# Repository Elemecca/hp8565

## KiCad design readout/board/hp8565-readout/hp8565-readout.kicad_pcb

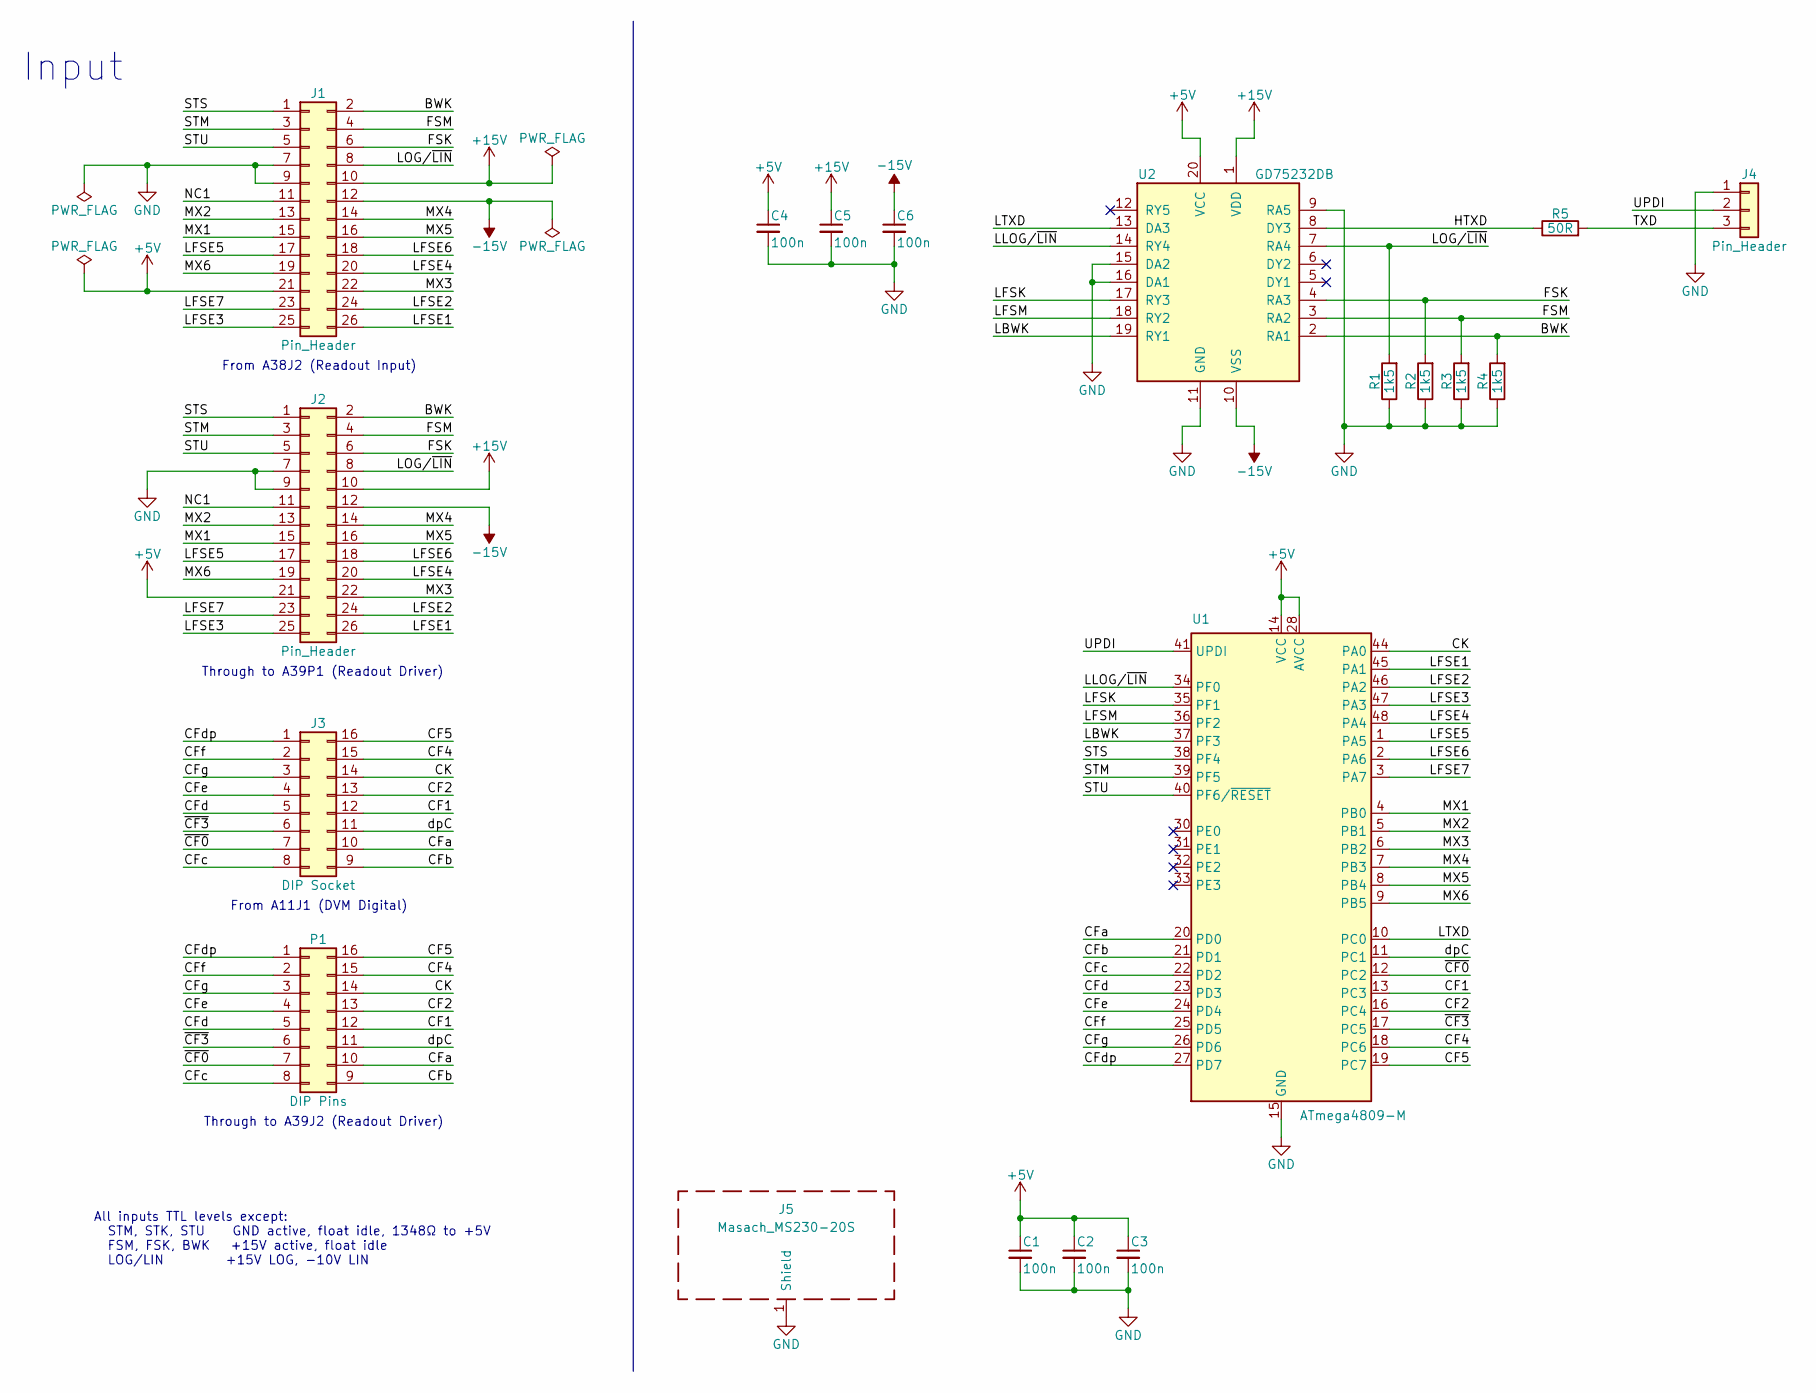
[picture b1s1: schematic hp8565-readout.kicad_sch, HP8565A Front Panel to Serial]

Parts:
C1, C2, C3, C4, C5, C6: 100n; C_0402_1005Metric
J1, J2: Pin_Header; PinHeader_2x13_P2.54mm_Vertical
J3: DIP Socket; DIP-16_W7.62mm_Socket
J4: Pin_Header; PinHeader_1x03_P2.54mm_Horizontal
J5: Masach_MS230-20S; Masach_MS230-20
P1: DIP Pins; DIP-16_W7.62mm
R1, R2, R3, R4: 1k5; R_0402_1005Metric
R5: 50R; R_0402_1005Metric
U1: ATmega4809-M; UQFN-48-1EP_6x6mm_P0.4mm_EP4.62x4.62mm
U2: GD75232DB; SSOP-20_4.4x6.5mm_P0.65mm

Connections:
+5V: C1.1, C2.1, C3.1, C4.1, J1.21, J2.21, U1.14 (VCC), U1.28 (AVCC), U1.42 (VCC), U2.20 (VCC)
+15V: C5.1, J1.10, J2.10, U2.1 (VDD)
-15V: C6.1, J1.12, J2.12, U2.10 (VSS)
/BWK: J1.2, J2.2, R4.2, U2.2 (RA1)
/CF1: J3.12, P1.12, U1.13 (PC3)
/CF2: J3.13, P1.13, U1.16 (PC4)
/CF4: J3.15, P1.15, U1.18 (PC6)
/CF5: J3.16, P1.16, U1.19 (PC7)
/CFa: J3.10, P1.10, U1.20 (PD0)
/CFb: J3.9, P1.9, U1.21 (PD1)
/CFc: J3.8, P1.8, U1.22 (PD2)
/CFd: J3.5, P1.5, U1.23 (PD3)
/CFdp: J3.1, P1.1, U1.27 (PD7)
/CFe: J3.4, P1.4, U1.24 (PD4)
/CFf: J3.2, P1.2, U1.25 (PD5)
/CFg: J3.3, P1.3, U1.26 (PD6)
/CK: J3.14, P1.14, U1.44 (PA0)
/FSK: J1.6, J2.6, R2.2, U2.4 (RA3)
/FSM: J1.4, J2.4, R3.2, U2.3 (RA2)
/HTXD: R5.1, U2.8 (DY3)
/LBWK: U1.37 (PF3), U2.19 (RY1)
/LFSE1: J1.26, J2.26, U1.45 (PA1)
/LFSE2: J1.24, J2.24, U1.46 (PA2)
/LFSE3: J1.25, J2.25, U1.47 (PA3)
/LFSE4: J1.20, J2.20, U1.48 (PA4)
/LFSE5: J1.17, J2.17, U1.1 (PA5)
/LFSE6: J1.18, J2.18, U1.2 (PA6)
/LFSE7: J1.23, J2.23, U1.3 (PA7)
/LFSK: U1.35 (PF1), U2.17 (RY3)
/LFSM: U1.36 (PF2), U2.18 (RY2)
/LLOG/~LIN: U1.34 (PF0), U2.14 (RY4)
/LOG/~LIN: J1.8, J2.8, R1.2, U2.7 (RA4)
/LTXD: U1.10 (PC0), U2.13 (DA3)
/MX1: J1.15, J2.15, U1.4 (PB0)
/MX2: J1.13, J2.13, U1.5 (PB1)
/MX3: J1.22, J2.22, U1.6 (PB2)
/MX4: J1.14, J2.14, U1.7 (PB3)
/MX5: J1.16, J2.16, U1.8 (PB4)
/MX6: J1.19, J2.19, U1.9 (PB5)
/NC1: J1.11, J2.11
/STM: J1.3, J2.3, U1.39 (PF5)
/STS: J1.1, J2.1, U1.38 (PF4)
/STU: J1.5, J2.5, U1.40 (PF6/~RESET)
/TXD: J4.3, R5.2
/UPDI: J4.2, U1.41 (UPDI)
/dpC: J3.11, P1.11, U1.11 (PC1)
/~CF0: J3.7, P1.7, U1.12 (PC2)
/~CF3: J3.6, P1.6, U1.17 (PC5)
GND: C1.2, C2.2, C3.2, C4.2, C5.2, C6.2, J1.7, J1.9, J2.7, J2.9, J4.1, J5.1 (Shield), R1.1, R2.1, R3.1, R4.1, U1.15 (GND), U1.29 (GND), U1.43 (GND), U1.49 (GND), U2.9 (RA5), U2.11 (GND), U2.15 (DA2), U2.16 (DA1)

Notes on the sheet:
From A38J2 (Readout Input)
From A11J1 (DVM Digital)
Through to A39J2 (Readout Driver)
Input
Through to A39P1 (Readout Driver)
All inputs TTL levels except: STM, STK, STU GND active, float idle, 1348Ω to +5V FSM, FSK, BWK +15V active, float idle LOG/LIN +15V LOG, -10V LIN

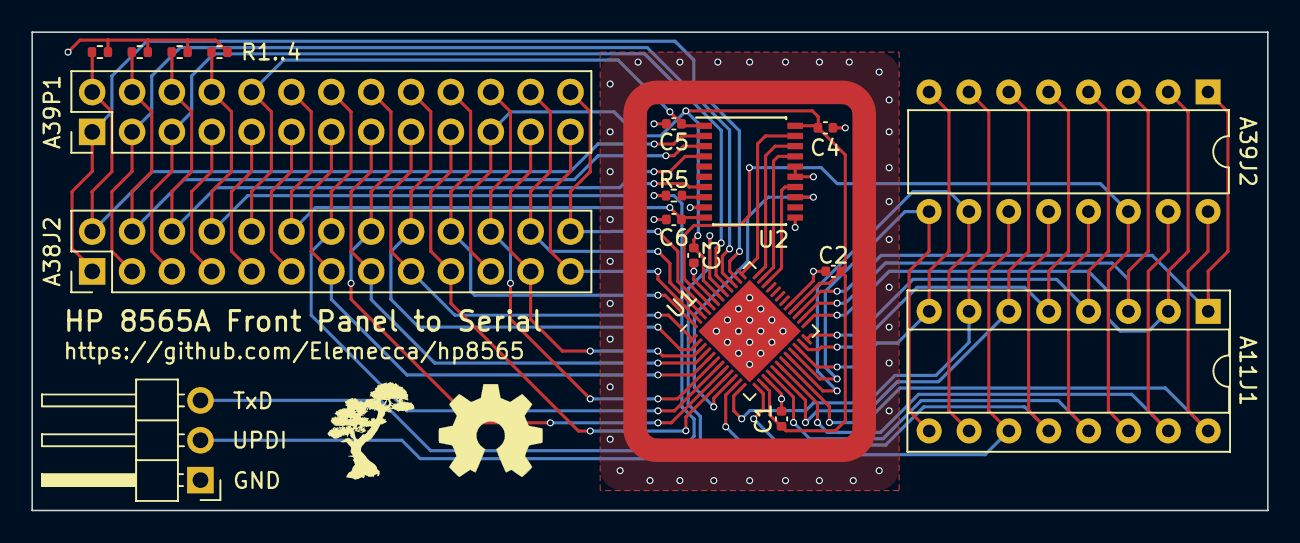
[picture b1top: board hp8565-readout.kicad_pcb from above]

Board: 4 copper layers, 78.7 x 30.5 mm, 19 parts (0 on the bottom side), 49 nets.

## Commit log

2023-07-07 Some notes on the front panel interface.
2023-07-07 Start on readount board.
2023-07-08 Route CF connector.
2023-07-08 Clean up silkscreen and stuff.
2023-07-09 Set up for production exports.
2023-08-10 First draft of mounting bracket.
2023-08-11 Second iteration of bracket.
2023-08-11 Working bracket.

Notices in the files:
readout/board/hp8565-readout/hp8565-readout.kicad_pcb:
© 2023 Sam Hanes, licensed under CERN-OHL-P v2
